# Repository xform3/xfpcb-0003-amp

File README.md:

# XFPCB-0003 Class-AB Amplifier 20-30W LM1875 or TDA2030

## Variation 1 LM1875
The LM1875 is a monolithic power amplifier offering very low distortion and high quality performance for consumer audio applications.
#### Specifications 
- Load: 4Ω - 8Ω 
- Output Power: 30W
- Supply Voltage 12V-36V(±18)
#### Features
- Low Distortion: 0.015%, 1 kHz, 20 W
- Wide Power Bandwidth: 70 kHz
- High Current Capability: 4A
- Protection for AC and DC Short Circuits to Ground

## Variation 2 TDA2030
The TDA2030 is a monolithic integrated circuit in Pentawattpackage, intended for use as a low frequency class AB amplifier.
#### Specifications 
- Load: 4Ω - 8Ω 
- Supply Voltage ±18(36)
- Output Power: 20W
#### Features
- Low harmonic and cross-over distortion
- Short circuit protection system and thermal shut-down system

### [Use with: XFPCB-0004 Regulated Bipolar Power Supply](https://github.com/xform3/xfpcb-0004-psu)

# Included Files:
* [xf3_amp](https://github.com/xform3/xfpcb-0003-amp/tree/master/xf3_amp)  - *KiCAD Project Files*
* [xf3_amp_gerbers_masks](https://github.com/xform3/xfpcb-0003-amp/tree/master/xf3_amp_gerbers_masks) - *PCB Gerber, Drill, Silk/Solder Masks, Positive and Negative plots*
* [xf3-KiCad-Library](https://github.com/xform3/xf3-KiCad-Library)  - *KiCAD Library Files; footprints, .step and .wrl component models, schema lib.*

## Schematic

## Application

## KiCad 3D

## PCB

## Prototype

## Amplifier [Using: XFPCB-0004 Regulated Bipolar Power Supply](https://github.com/xform3/xfpcb-0004-psu)

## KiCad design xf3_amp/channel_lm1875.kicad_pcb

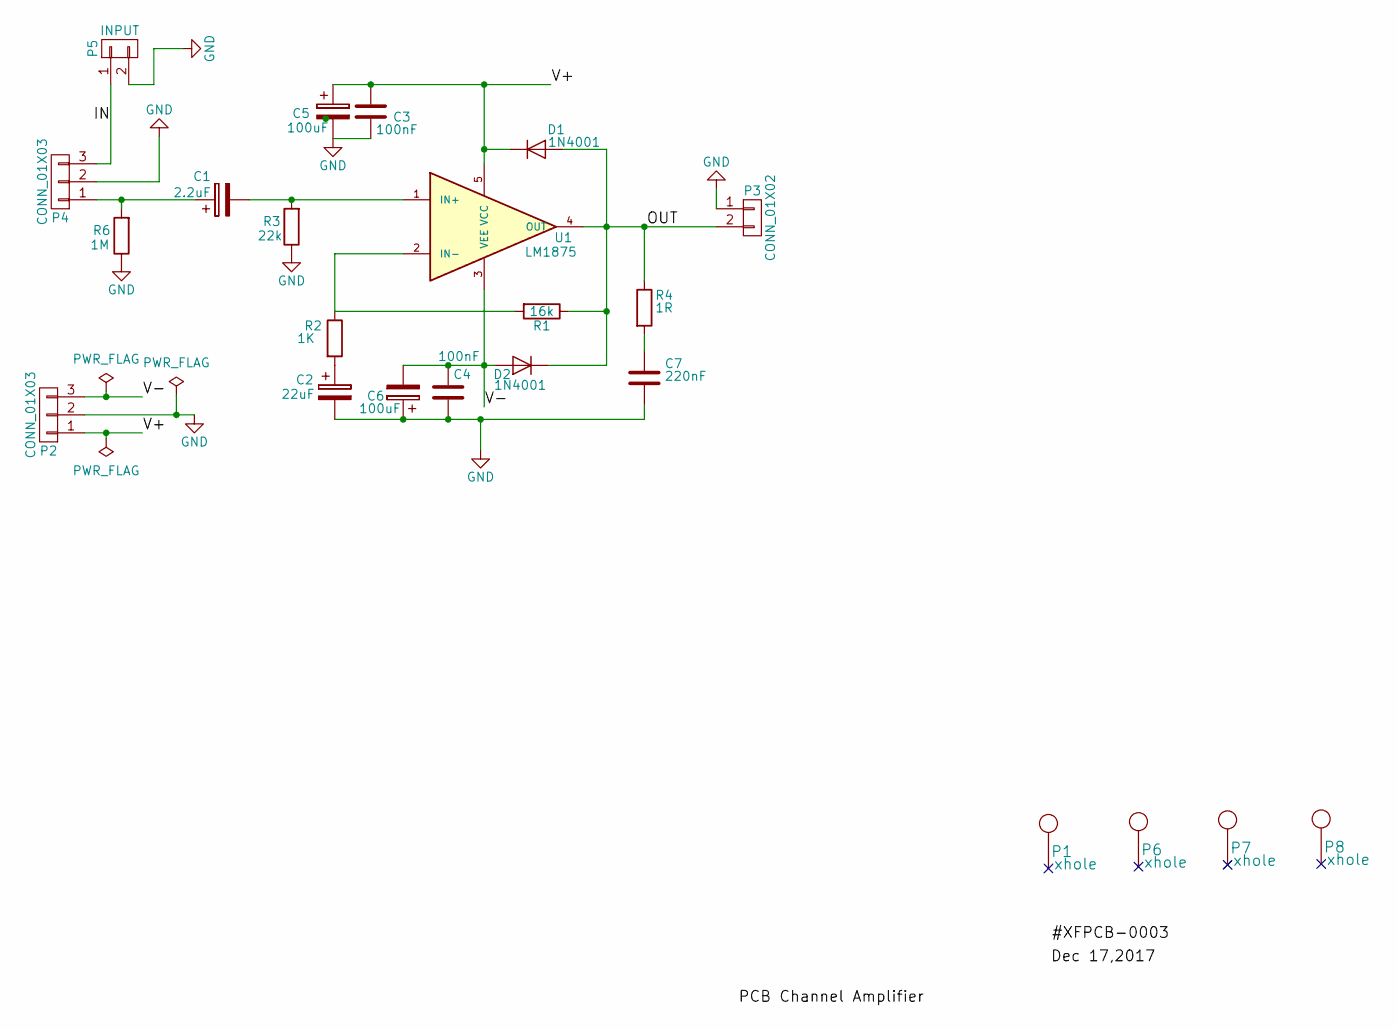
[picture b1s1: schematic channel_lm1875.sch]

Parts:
C1: 2.2uF; x_CapRadial7mm
C2: 22uF; x_CapRadial7mm
C3, C4: 100nF; x_CapDisk9mm
C5, C6: 100uF; x_CapRadial7mm
C7: 220nF; x_CapDisk9mm
D1, D2: 1N4001; x_Diode
P1, P6, P7, P8: xhole; x_HoleRound
P2: CONN_01X03; x_PhoenixX3
P3: CONN_01X02; x_PhoenixX2
P4: CONN_01X03; x_PotConn
P5: INPUT; x_PhoenixX2mini
R1: 16k; x_ResistorHorizontalRM10mm
R2: 1K; x_ResistorHorizontalRM10mm
R3: 22k; x_ResistorHorizontalRM10mm
R4: 1R; x_ResistorHorizontalRM10mm
R6: 1M; x_ResistorHorizontalRM10mm
U1: LM1875; x_TDA

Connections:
/IN: P4.3, P5.1
/OUT: D1.2 (A), D2.1 (K), P3.2, R1.1, R4.1, U1.4 (OUT)
/V+: C3.1, C5.1, D1.1 (K), P2.1, U1.5 (VCC)
/V-: C4.1, C6.2, D2.2 (A), P2.3, U1.3 (VEE)
GND: C2.2, C3.2, C4.2, C5.2, C6.1, C7.2, P2.2, P3.1, P4.2, P5.2, R3.1, R6.1
unnamed: C1.1, P4.1, R6.2
unnamed: C1.2, R3.2, U1.1 (IN+)
unnamed: C2.1, R2.2
unnamed: C7.1, R4.2
unnamed: R1.2, R2.1, U1.2 (IN-)

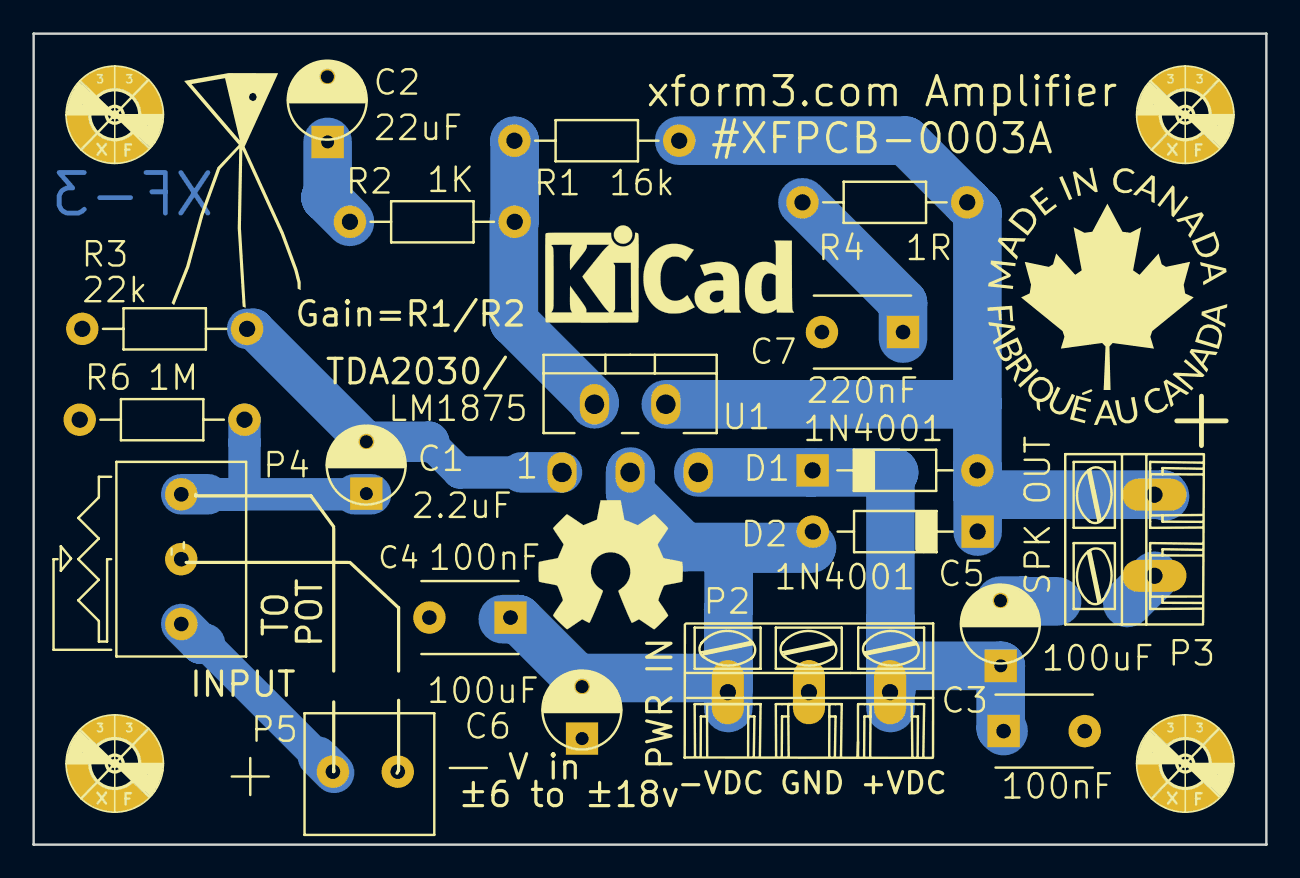
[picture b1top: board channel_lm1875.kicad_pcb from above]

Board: 2 copper layers, 76.0 x 50.0 mm, 25 parts (0 on the bottom side), 10 nets.

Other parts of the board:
svg2mod: G***; x_gx_xform_8x14_Silk
svg2mod#2: G***; x_gx_madeincanada

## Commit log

2018-06-08 added pictures, updated pcb, silk
2018-06-08 adde pictures
2018-06-08 adde picture
